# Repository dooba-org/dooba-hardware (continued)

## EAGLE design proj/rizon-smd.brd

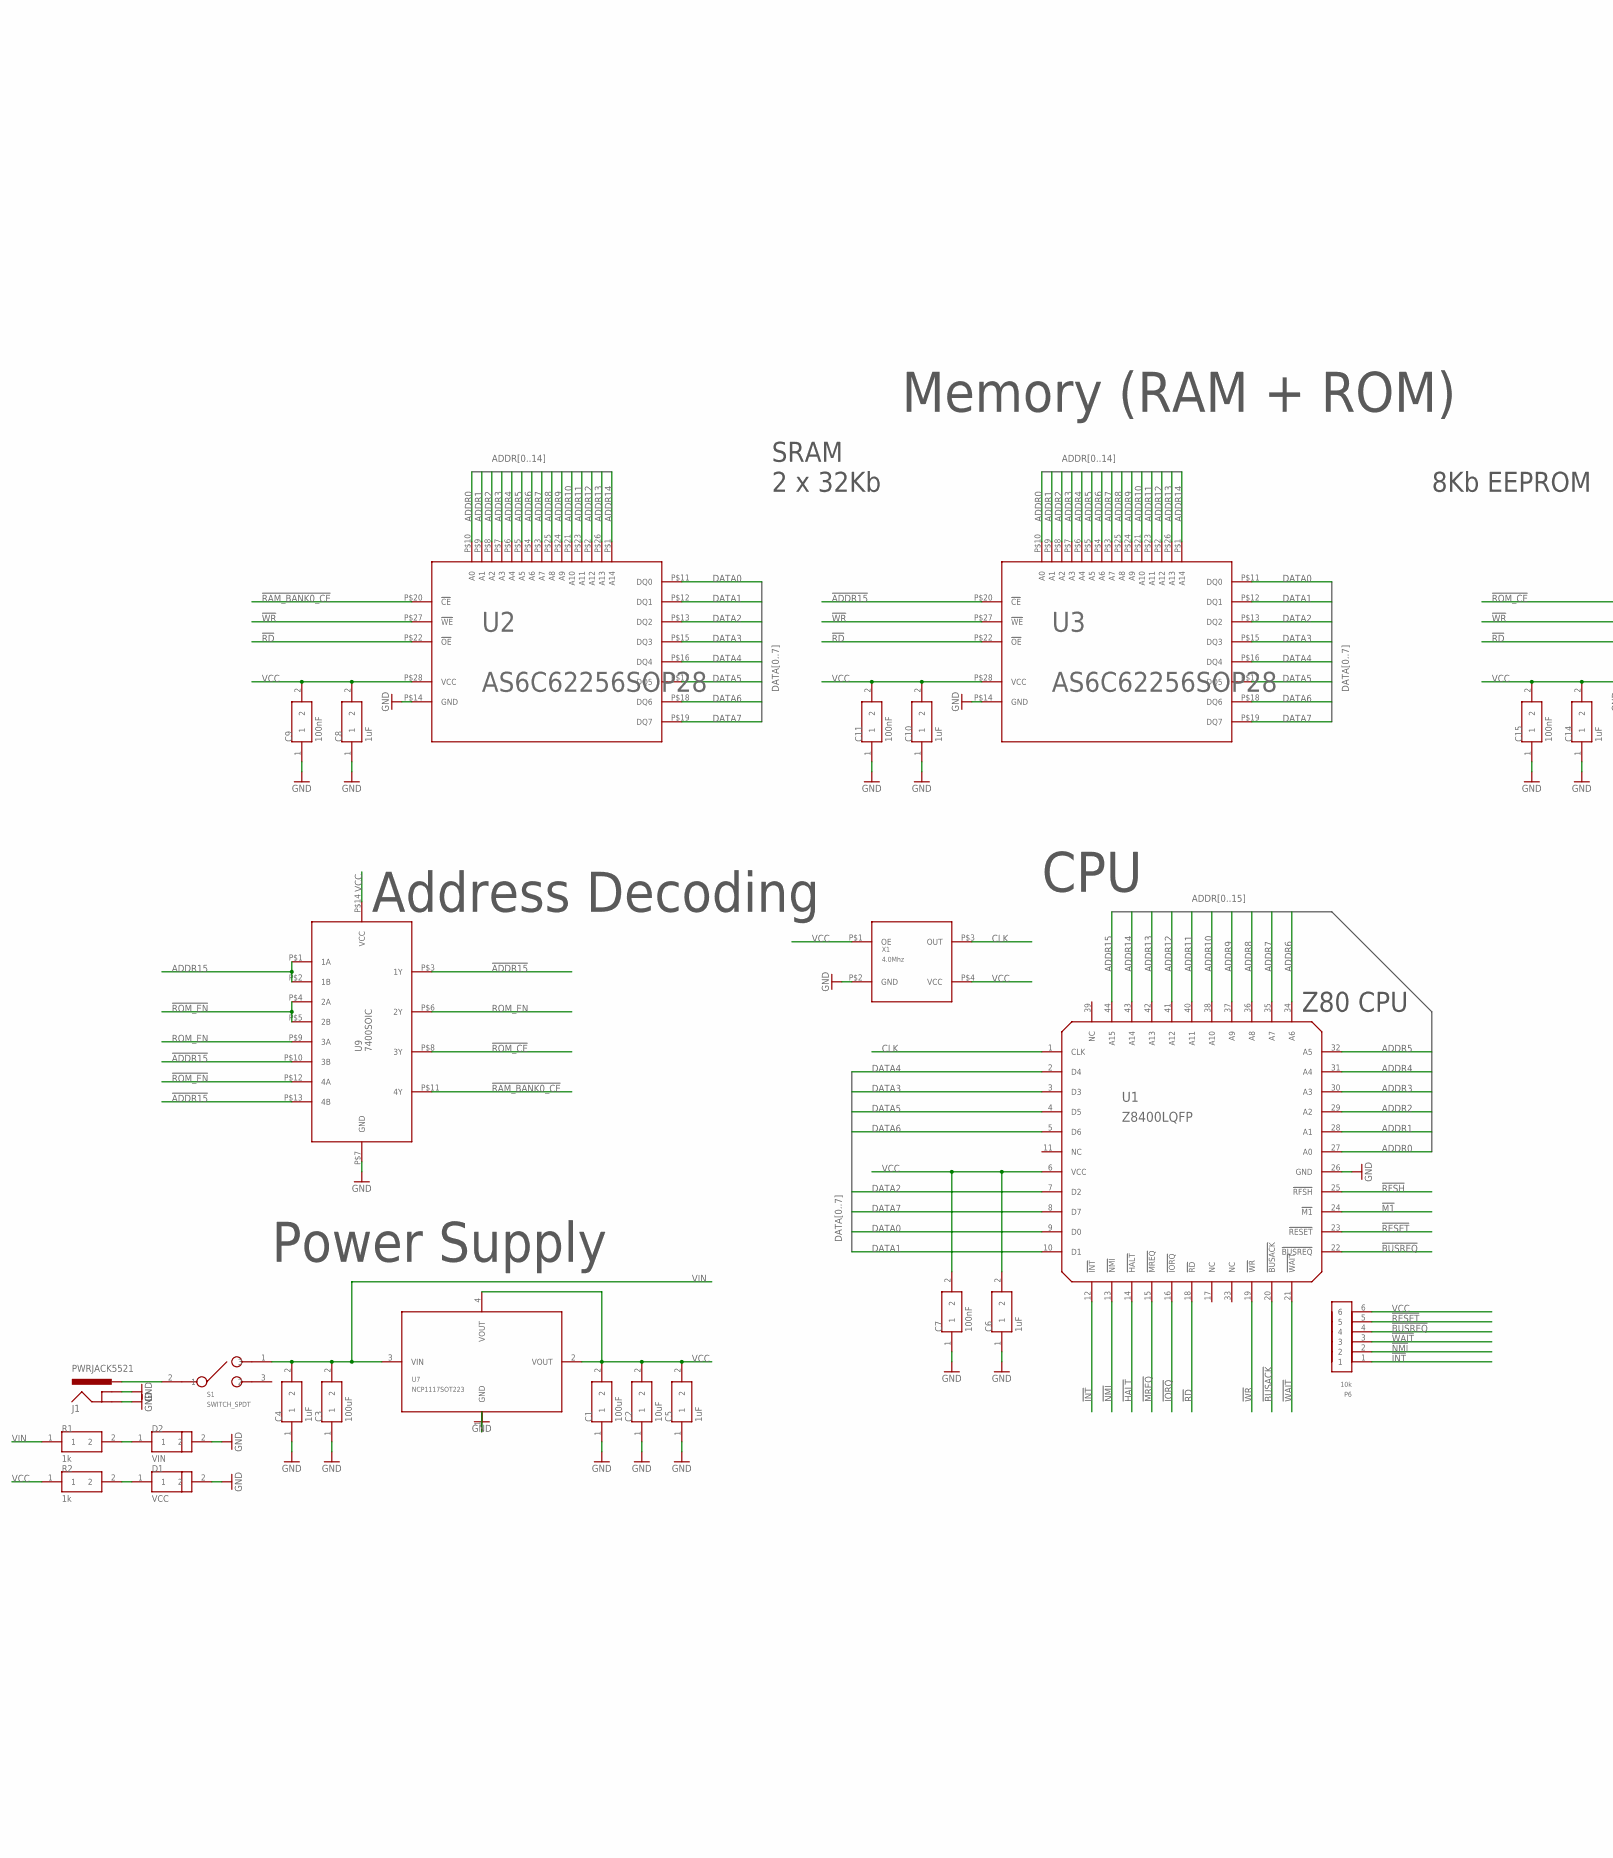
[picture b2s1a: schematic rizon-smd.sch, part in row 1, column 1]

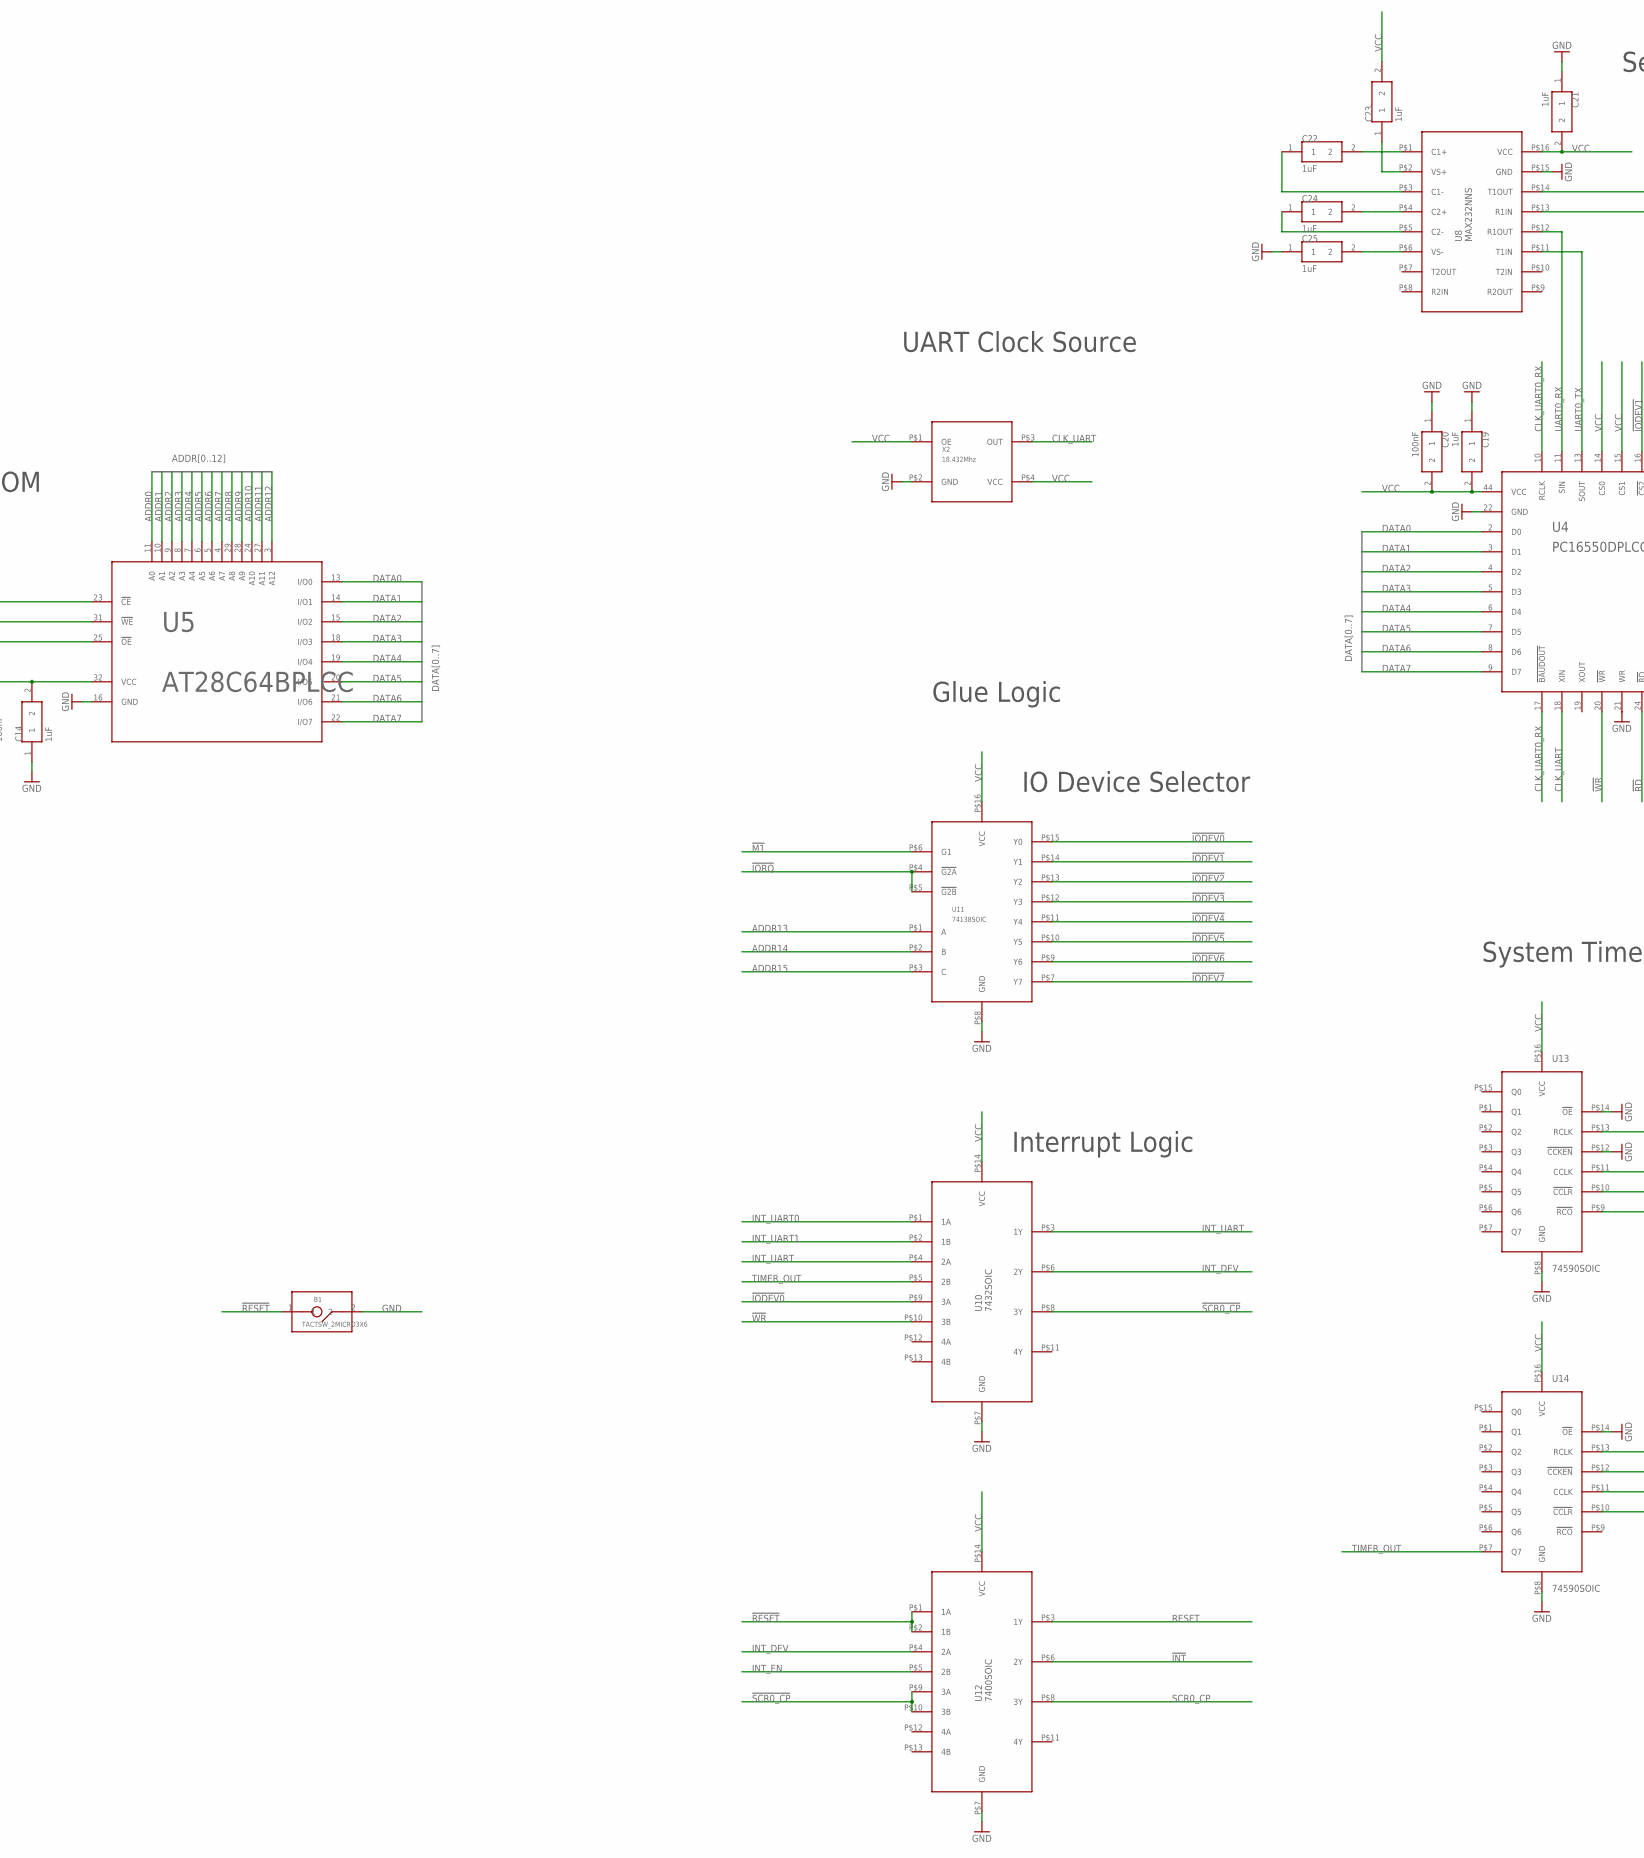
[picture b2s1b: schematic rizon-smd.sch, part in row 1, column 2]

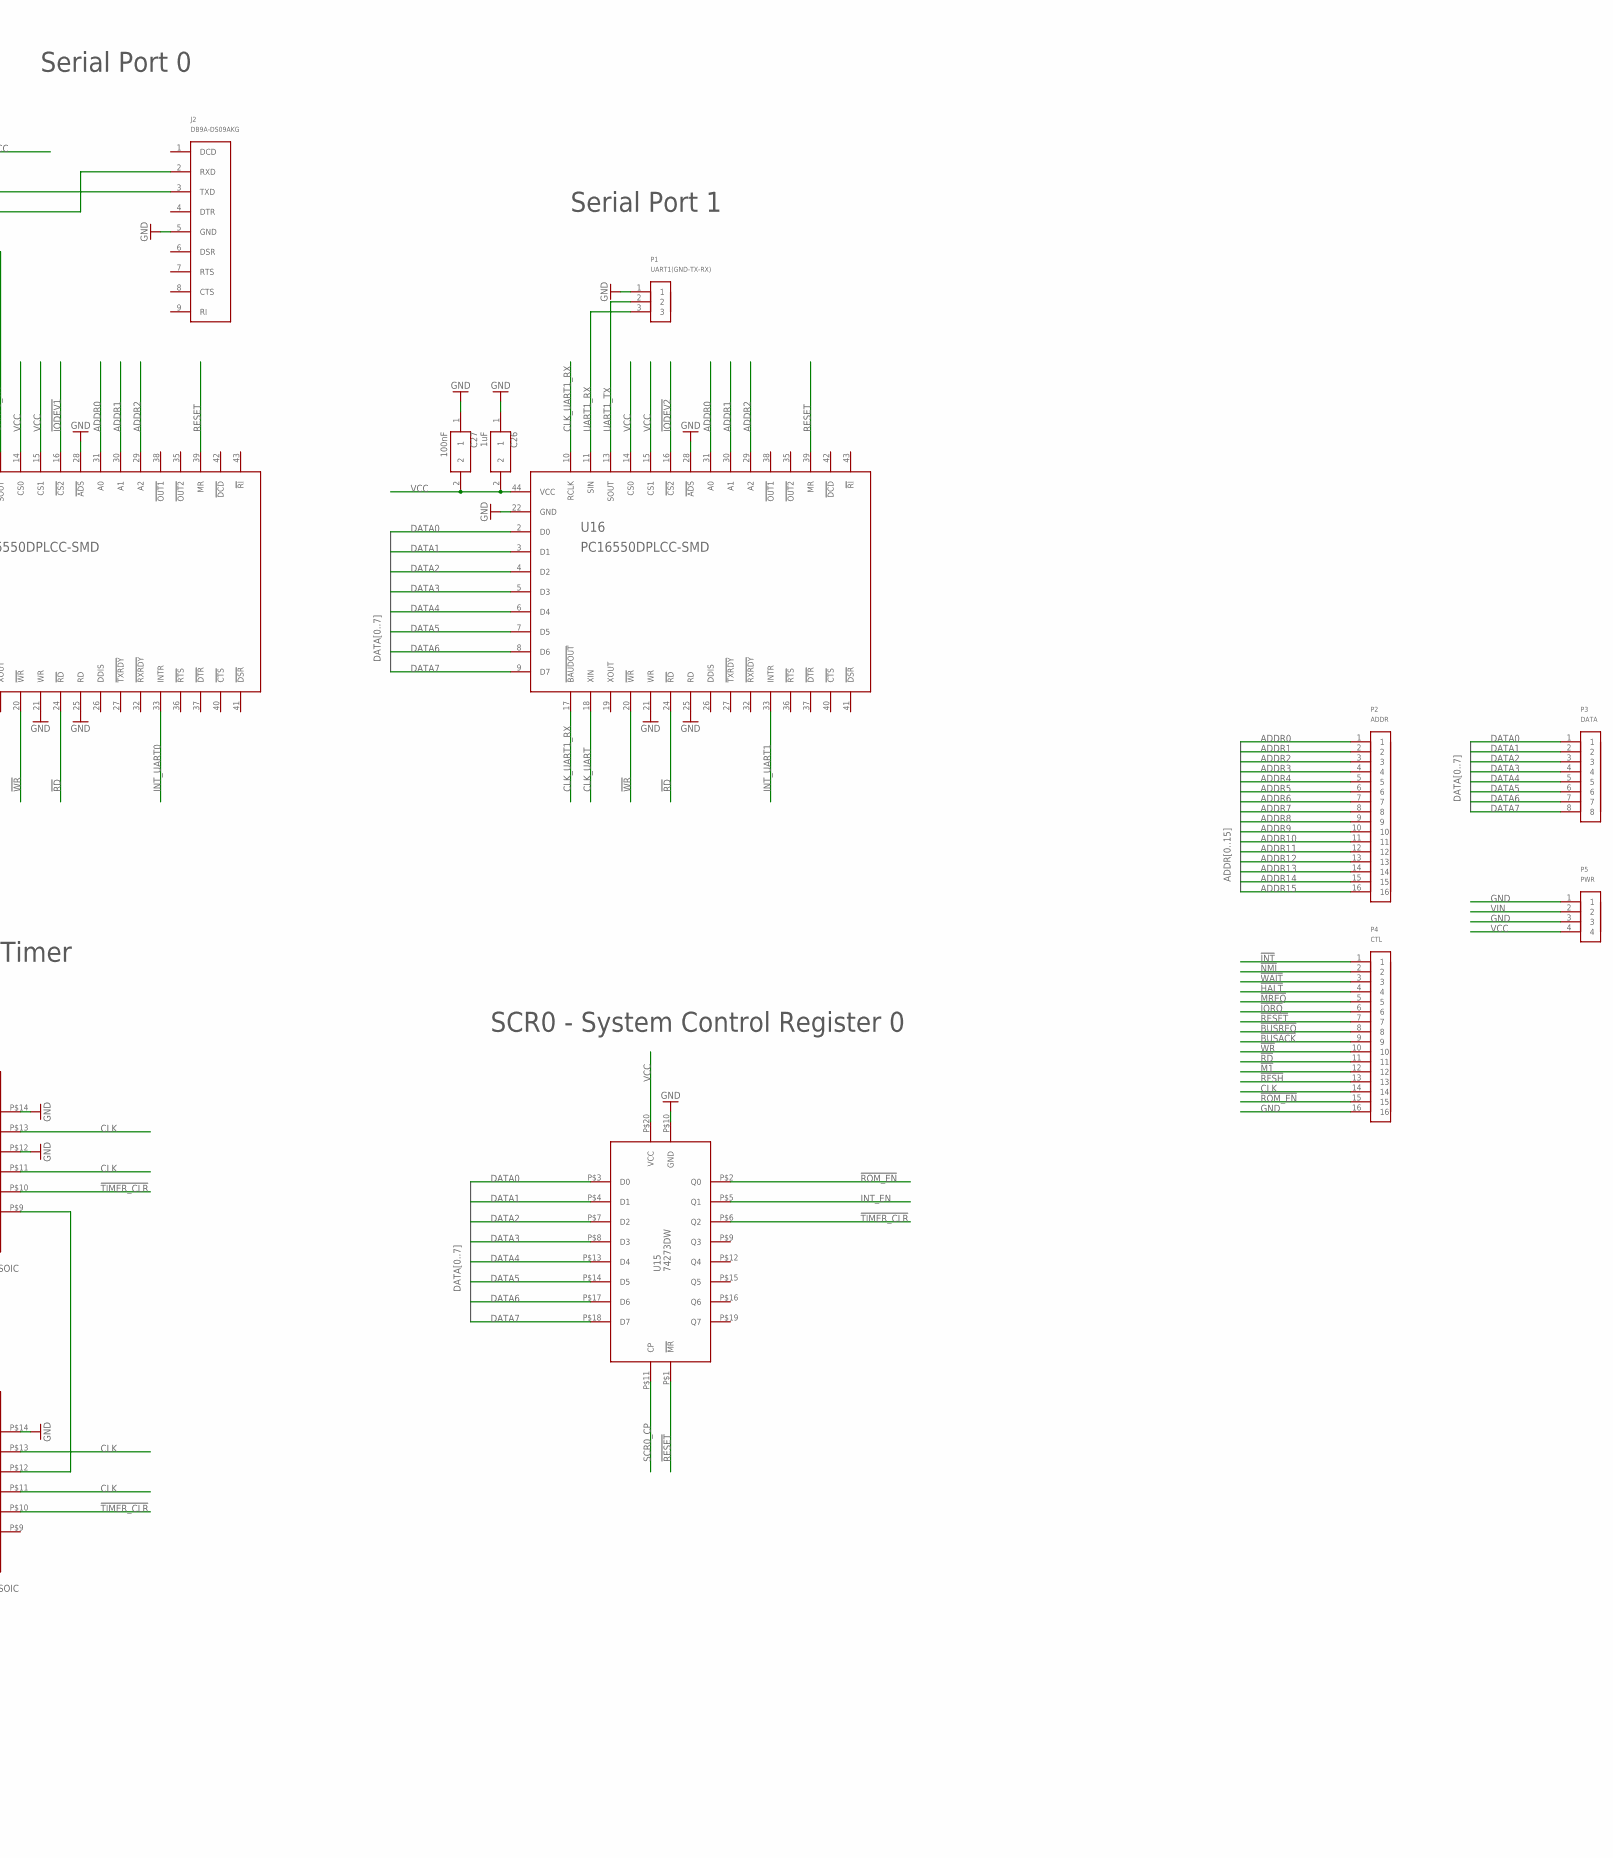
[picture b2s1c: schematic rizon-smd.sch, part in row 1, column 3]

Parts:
B1: TACTSW_2MICRO3X6; TACTSW_MICRO3X6
C1, C3: 100uF; 1210
C2: 10uF; 0805
C4, C5, C6, C8, C10, C14, C19, C21, C22, C23, C24, C25, C26: 1uF; 0805
C7, C9, C11, C15, C20, C27: 100nF; 0805
D1: VCC; 0805
D2: VIN; 0805
J1: PWRJACK5521; PWRJACK_5521
J2: DB9A-DS09AKG; A-DS09AKG
P1: UART1(GND-TX-RX); PIN_3
P2: ADDR; PIN_16
P3: DATA; PIN_8
P4: CTL; PIN_16
P5: PWR; PIN_4
P6: 10k; PIN_6
R1, R2: 1k; 0805
S1: SWITCH_SPDT; JS102011
U1: Z8400LQFP; QFP44
U2, U3: AS6C62256SOP28; SOP28
U4, U16: PC16550DPLCC-SMD; PLCC44
U5: AT28C64BPLCC; PLCC-S32--SOCKET
U7: NCP1117SOT223; SOT223
U8: MAX232NNS; SO16
U9, U12: 7400SOIC; SOIC14
U10: 7432SOIC; SOIC14
U11: 74138SOIC; SOIC16
U13, U14: 74590SOIC; SOIC16
U15: 74273DW; SO20
X1: 4.0Mhz; OSC4-SMD-7X5
X2: 18.432Mhz; OSC4-SMD-7X5

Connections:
!ADDR15: U3.P$20 (!CE), U9.P$3 (1Y), U9.P$10 (3B), U9.P$13 (4B)
!BUSACK: P4.9, U1.20 (!BUSACK)
!BUSREQ: P4.8, P6.4, U1.22 (!BUSREQ)
!HALT: P4.4, U1.14 (!HALT)
!INT: P4.1, P6.1, U1.12 (!INT), U12.P$6 (2Y)
!IODEV0: U10.P$9 (3A), U11.P$15 (Y0)
!IODEV1: U4.16 (!CS2), U11.P$14 (Y1)
!IODEV2: U11.P$13 (Y2), U16.16 (!CS2)
!IODEV3: U11.P$12 (Y3)
!IODEV4: U11.P$11 (Y4)
!IODEV5: U11.P$10 (Y5)
!IODEV6: U11.P$9 (Y6)
!IODEV7: U11.P$7 (Y7)
!IORQ: P4.6, U1.16 (!IORQ), U11.P$4 (!G2A), U11.P$5 (!G2B)
!M1: P4.12, U1.24 (!M1), U11.P$6 (G1)
!MREQ: P4.5, U1.15 (!MREQ)
!NMI: P4.2, P6.2, U1.13 (!NMI)
!RAM_BANK0_CE: U2.P$20 (!CE), U9.P$11 (4Y)
!RD: P4.11, U1.18 (!RD), U2.P$22 (!OE), U3.P$22 (!OE), U4.24 (!RD), U5.25 (!OE), U16.24 (!RD)
!RESET: B1.1, P4.7, P6.5, U1.23 (!RESET), U12.P$1 (1A), U12.P$2 (1B), U15.P$1 (!MR)
!RFSH: P4.13, U1.25 (!RFSH)
!ROM_CE: U5.23 (!CE), U9.P$8 (3Y)
!ROM_EN: P4.15, U9.P$4 (2A), U9.P$5 (2B), U9.P$12 (4A), U15.P$2 (Q0)
!SCR0_CP: U10.P$8 (3Y), U12.P$9 (3A), U12.P$10 (3B)
!TIMER_CLR: U13.P$10 (!CCLR), U14.P$10 (!CCLR), U15.P$6 (Q2)
!WAIT: P4.3, P6.3, U1.21 (!WAIT)
!WR: P4.10, U1.19 (!WR), U2.P$27 (!WE), U3.P$27 (!WE), U4.20 (!WR), U5.31 (!WE), U10.P$10 (3B), U16.20 (!WR)
ADDR0: P2.1, U1.27 (A0), U2.P$10 (A0), U3.P$10 (A0), U4.31 (A0), U5.11 (A0), U16.31 (A0)
ADDR1: P2.2, U1.28 (A1), U2.P$9 (A1), U3.P$9 (A1), U4.30 (A1), U5.10 (A1), U16.30 (A1)
ADDR2: P2.3, U1.29 (A2), U2.P$8 (A2), U3.P$8 (A2), U4.29 (A2), U5.9 (A2), U16.29 (A2)
ADDR3: P2.4, U1.30 (A3), U2.P$7 (A3), U3.P$7 (A3), U5.8 (A3)
ADDR4: P2.5, U1.31 (A4), U2.P$6 (A4), U3.P$6 (A4), U5.7 (A4)
ADDR5: P2.6, U1.32 (A5), U2.P$5 (A5), U3.P$5 (A5), U5.6 (A5)
ADDR6: P2.7, U1.34 (A6), U2.P$4 (A6), U3.P$4 (A6), U5.5 (A6)
ADDR7: P2.8, U1.35 (A7), U2.P$3 (A7), U3.P$3 (A7), U5.4 (A7)
ADDR8: P2.9, U1.36 (A8), U2.P$25 (A8), U3.P$25 (A8), U5.29 (A8)
ADDR9: P2.10, U1.37 (A9), U2.P$24 (A9), U3.P$24 (A9), U5.28 (A9)
ADDR10: P2.11, U1.38 (A10), U2.P$21 (A10), U3.P$21 (A10), U5.24 (A10)
ADDR11: P2.12, U1.40 (A11), U2.P$23 (A11), U3.P$23 (A11), U5.27 (A11)
ADDR12: P2.13, U1.41 (A12), U2.P$2 (A12), U3.P$2 (A12), U5.3 (A12)
ADDR13: P2.14, U1.42 (A13), U2.P$26 (A13), U3.P$26 (A13), U11.P$1 (A)
ADDR14: P2.15, U1.43 (A14), U2.P$1 (A14), U3.P$1 (A14), U11.P$2 (B)
ADDR15: P2.16, U1.44 (A15), U9.P$1 (1A), U9.P$2 (1B), U11.P$3 (C)
CLK: P4.14, U1.1 (CLK), U13.P$11 (CCLK), U13.P$13 (RCLK), U14.P$11 (CCLK), U14.P$13 (RCLK), X1.P$3 (OUT)
CLK_UART: U4.18 (XIN), U16.18 (XIN), X2.P$3 (OUT)
CLK_UART0_RX: U4.10 (RCLK), U4.17 (!BAUDOUT)
CLK_UART1_RX: U16.10 (RCLK), U16.17 (!BAUDOUT)
DATA0: P3.1, U1.9 (D0), U2.P$11 (DQ0), U3.P$11 (DQ0), U4.2 (D0), U5.13 (I/O0), U15.P$3 (D0), U16.2 (D0)
DATA1: P3.2, U1.10 (D1), U2.P$12 (DQ1), U3.P$12 (DQ1), U4.3 (D1), U5.14 (I/O1), U15.P$4 (D1), U16.3 (D1)
DATA2: P3.3, U1.7 (D2), U2.P$13 (DQ2), U3.P$13 (DQ2), U4.4 (D2), U5.15 (I/O2), U15.P$7 (D2), U16.4 (D2)
DATA3: P3.4, U1.3 (D3), U2.P$15 (DQ3), U3.P$15 (DQ3), U4.5 (D3), U5.18 (I/O3), U15.P$8 (D3), U16.5 (D3)
DATA4: P3.5, U1.2 (D4), U2.P$16 (DQ4), U3.P$16 (DQ4), U4.6 (D4), U5.19 (I/O4), U15.P$13 (D4), U16.6 (D4)
DATA5: P3.6, U1.4 (D5), U2.P$17 (DQ5), U3.P$17 (DQ5), U4.7 (D5), U5.20 (I/O5), U15.P$14 (D5), U16.7 (D5)
DATA6: P3.7, U1.5 (D6), U2.P$18 (DQ6), U3.P$18 (DQ6), U4.8 (D6), U5.21 (I/O6), U15.P$17 (D6), U16.8 (D6)
DATA7: P3.8, U1.8 (D7), U2.P$19 (DQ7), U3.P$19 (DQ7), U4.9 (D7), U5.22 (I/O7), U15.P$18 (D7), U16.9 (D7)
GND: B1.2, C1.1, C2.1, C3.1, C4.1, C5.1, C6.1, C7.1, C8.1, C9.1, C10.1, C11.1, C14.1, C15.1, C19.1, C20.1, C21.1, C25.1, C26.1, C27.1, D1.2, D2.2, J1.GND, J1.GNDBREAK, J2.5 (GND), P1.1, P4.16, P5.1, P5.3, U1.26 (GND), U2.P$14 (GND), U3.P$14 (GND), U4.21 (WR), U4.22 (GND), U4.25 (RD), U4.28 (!ADS), U5.16 (GND), U7.1 (GND), U8.P$15 (GND), U9.P$7 (GND), U10.P$7 (GND), U11.P$8 (GND), U12.P$7 (GND), U13.P$8 (GND), U13.P$12 (!CCKEN), U13.P$14 (!OE), U14.P$8 (GND), U14.P$14 (!OE), U15.P$10 (GND), U16.21 (WR), U16.22 (GND), U16.25 (RD), U16.28 (!ADS), X1.P$2 (GND), X2.P$2 (GND)
INT_DEV: U10.P$6 (2Y), U12.P$4 (2A)
INT_EN: U12.P$5 (2B), U15.P$5 (Q1)
INT_UART: U10.P$3 (1Y), U10.P$4 (2A)
INT_UART0: U4.33 (INTR), U10.P$1 (1A)
INT_UART1: U10.P$2 (1B), U16.33 (INTR)
unnamed: D2.1, R1.2
unnamed: D1.1, R2.2
unnamed: U13.P$9 (!RCO), U14.P$12 (!CCKEN)
unnamed: J1.PWR, S1.2 (1)
unnamed: C24.2, U8.P$4 (C2+)
unnamed: C24.1, U8.P$5 (C2-)
unnamed: C22.1, U8.P$3 (C1-)
unnamed: C22.2, U8.P$1 (C1+)
unnamed: C23.1, U8.P$2 (VS+)
unnamed: C25.2, U8.P$6 (VS-)
unnamed: J2.3 (TXD), U8.P$14 (T1OUT)
unnamed: J2.2 (RXD), U8.P$13 (R1IN)
RESET: U4.39 (MR), U12.P$3 (1Y), U16.39 (MR)
ROM_EN: U9.P$6 (2Y), U9.P$9 (3A)
SCR0_CP: U12.P$8 (3Y), U15.P$11 (CP)
TIMER_OUT: U10.P$5 (2B), U14.P$7 (Q7)
UART0_RX: U4.11 (SIN), U8.P$12 (R1OUT)
UART0_TX: U4.13 (SOUT), U8.P$11 (T1IN)
UART1_RX: P1.3, U16.11 (SIN)
UART1_TX: P1.2, U16.13 (SOUT)
VCC: C1.2, C2.2, C5.2, C6.2, C7.2, C8.2, C9.2, C10.2, C11.2, C14.2, C15.2, C19.2, C20.2, C21.2, C23.2, C26.2, C27.2, P5.4, P6.6, R2.1, U1.6 (VCC), U2.P$28 (VCC), U3.P$28 (VCC), U4.14 (CS0), U4.15 (CS1), U4.44 (VCC), U5.32 (VCC), U7.2 (VOUT), U7.4 (VOUT), U8.P$16 (VCC), U9.P$14 (VCC), U10.P$14 (VCC), U11.P$16 (VCC), U12.P$14 (VCC), U13.P$16 (VCC), U14.P$16 (VCC), U15.P$20 (VCC), U16.14 (CS0), U16.15 (CS1), U16.44 (VCC), X1.P$1 (OE), X1.P$4 (VCC), X2.P$1 (OE), X2.P$4 (VCC)
VIN: C3.2, C4.2, P5.2, R1.1, S1.1 (3), U7.3 (VIN)

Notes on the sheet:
SRAM 2 x 32Kb
8Kb EEPROM
Z80 CPU
Address Decoding
Memory (RAM + ROM)
Power Supply
CPU
IO Device Selector
Serial Port 0
UART Clock Source
System Timer
SCR0 - System Control Register 0
Glue Logic
Interrupt Logic
Serial Port 1

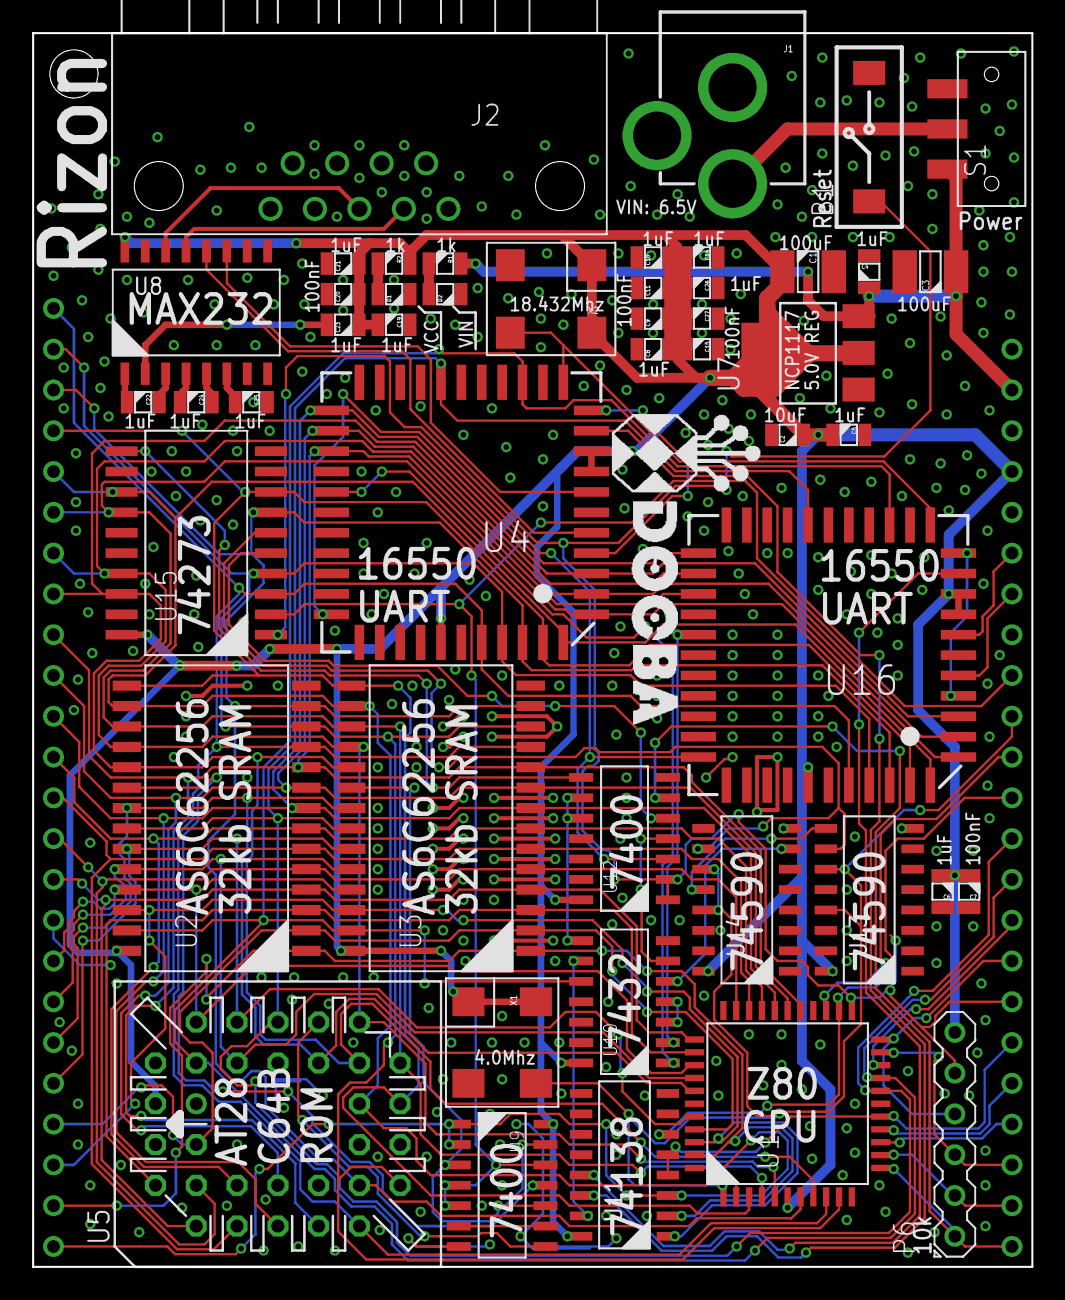
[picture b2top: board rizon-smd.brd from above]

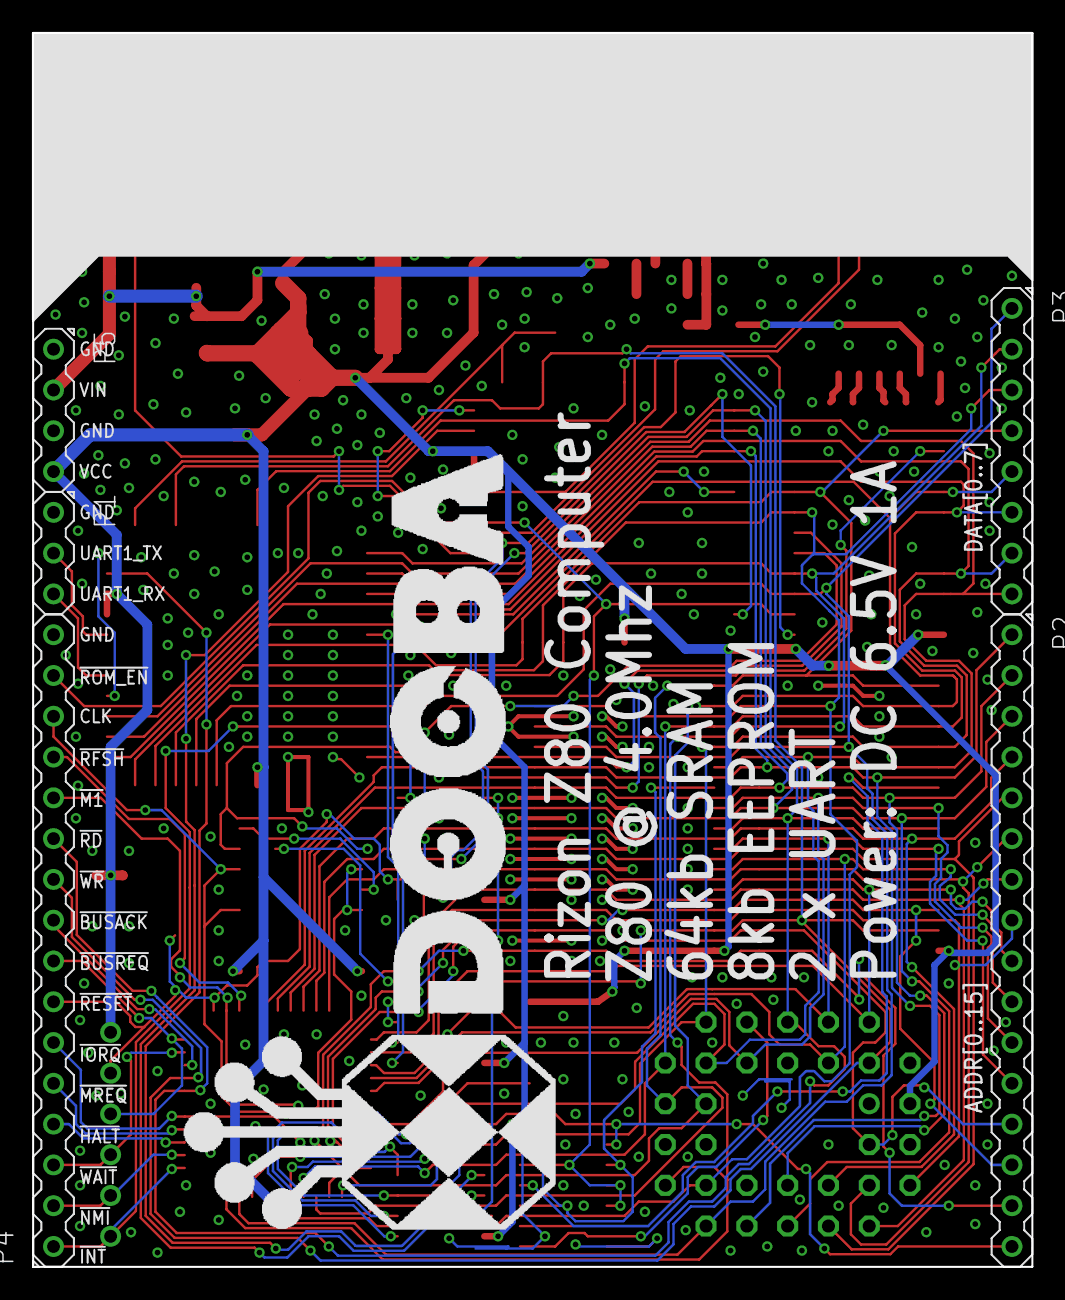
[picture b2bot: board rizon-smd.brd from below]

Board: 2 copper layers, 62.2 x 76.8 mm, 53 parts (5 on the bottom side), 78 nets.
